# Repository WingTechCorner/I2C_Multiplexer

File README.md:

# Wing's I2C Multiplexer

- Multiple I2C devices with the same address on the same bus.
- Not full duplex. Only one device active at any one time.
- Performs MUX'ing via 4052D IC

# Files/Folders

- `platformio.ini` PlatformIO project config file
- `./src/` Source code
- `./hardware/` Various hardware design files.

# Datasheets

- 4052D Dual 4-Channel Analog Multiplexer, Demultiplexer
  - [Nexperia 74HC4052D Datasheet from LCSC](https://datasheet.lcsc.com/szlcsc/Nexperia-74HC4052D-653_C11350.pdf)

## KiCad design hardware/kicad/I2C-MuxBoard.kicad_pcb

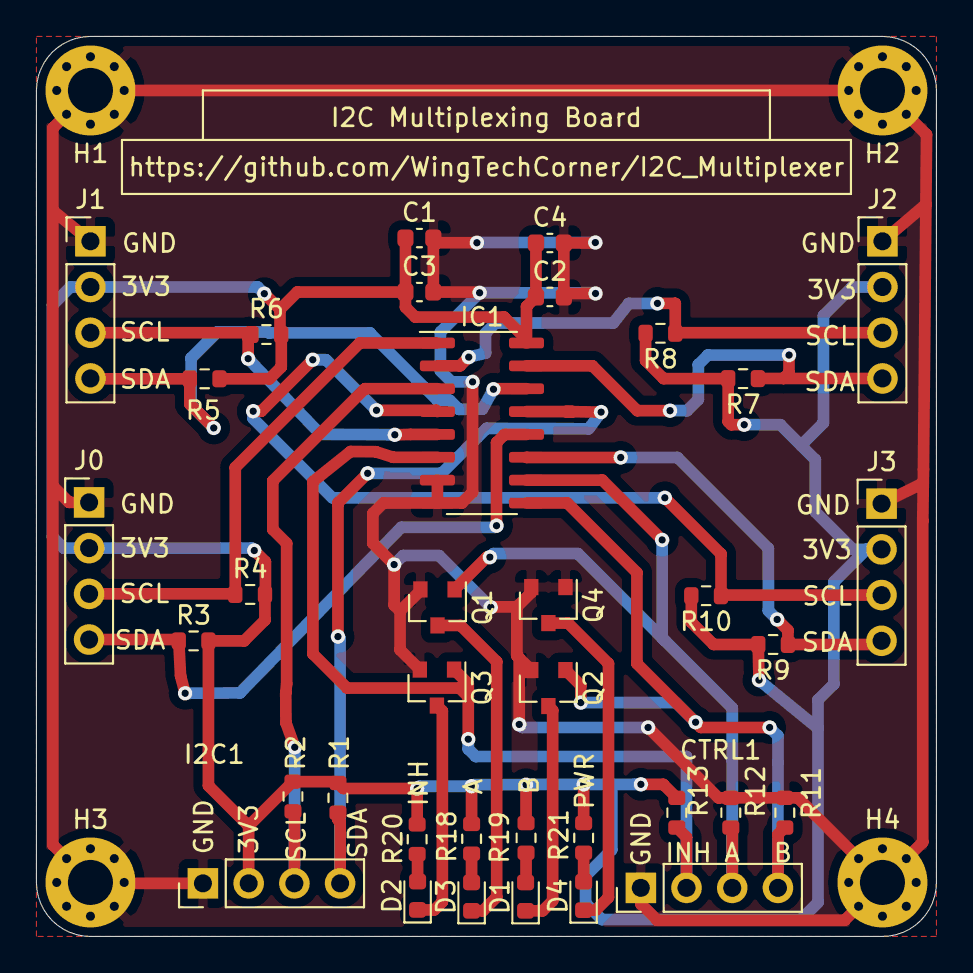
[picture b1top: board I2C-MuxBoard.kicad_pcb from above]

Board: 2 copper layers, 50.0 x 50.0 mm, 40 parts (0 on the bottom side), 23 nets.

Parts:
C1, C3: 4.7nF-50V-0603; C_0603_1608Metric
C2, C4: 10nF-50V-0603; C_0603_1608Metric
CTRL1: Conn_01x04; PinHeader_1x04_P2.54mm_Vertical
D1, D2, D3, D4: BLUE_LED; D_0603_1608Metric
H1, H2, H3, H4: MountingHole_Pad; MountingHole_2.5mm_Pad_Via
I2C1: Conn_01x04; PinHeader_1x04_P2.54mm_Vertical
IC1: CD4052B; SOIC-16_3.9x9.9mm_P1.27mm
J0, J1, J2, J3: Conn_01x04; PinHeader_1x04_P2.54mm_Vertical
Q1, Q2, Q3, Q4: AO3400A; SOT-23
R1, R2, R3, R4, R5, R6, R7, R8, R9, R10, R11, R12, R13: 10KOhms-±1%-1_10W-0603; R_0603_1608Metric
R18, R19, R20, R21: 470Ohms-±1%-1_10W-0603; R_0603_1608Metric

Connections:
3V3: C1.1, C2.1, C3.1, C4.1, I2C1.2, IC1.16, J0.2, J1.2, J2.2, J3.2, R1.2, R2.2, R3.2, R4.2, R5.2, R6.2, R7.2, R8.2, R9.2, R10.2, R13.2, R18.1, R19.1, R20.1, R21.1
ADDR-A: CTRL1.3, IC1.10, Q1.1, R12.1
ADDR-B: CTRL1.4, IC1.9, Q2.1, R11.1
GND: C1.2, C2.2, C3.2, C4.2, CTRL1.1, H1.1, H2.1, H3.1, H4.1, I2C1.1, IC1.7, IC1.8, J0.1, J1.1, J2.1, J3.1, Q1.2, Q2.2, Q3.2, Q4.1, Q4.2, R11.2, R12.2
INH: CTRL1.2, IC1.6, Q3.1, R13.1
unnamed: D1.1, Q2.3
unnamed: D1.2, R19.2
unnamed: D2.1, Q3.3
unnamed: D2.2, R20.2
unnamed: D3.1, Q1.3
unnamed: D3.2, R18.2
unnamed: D4.1, Q4.3
unnamed: D4.2, R21.2
P0-SCL: IC1.1, J0.3, R4.1
P0-SDA: IC1.12, J0.4, R3.1
P1-SCL: IC1.5, J1.3, R6.1
P1-SDA: IC1.14, J1.4, R5.1
P2-SCL: IC1.2, J2.3, R8.1
P2-SDA: IC1.15, J2.4, R7.1
P3-SCL: IC1.4, J3.3, R10.1
P3-SDA: IC1.11, J3.4, R9.1
SCL: I2C1.3, IC1.3, R2.1
SDA: I2C1.4, IC1.13, R1.1

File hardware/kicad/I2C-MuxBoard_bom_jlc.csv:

"Comment","Designator","Footprint","LCSC Part #"
"4.7nF-50V-0603","C1,C3","C_0603_1608Metric","C53987"
"10nF-50V-0603","C2,C4","C_0603_1608Metric","C57112"
"BLUE_LED","D1,D3,D2,D4","D_0603_1608Metric","C72041"
"CD4052B","IC1","SOIC-16_3.9x9.9mm_P1.27mm","C6521"
"AO3400A","Q2,Q3,Q1,Q4","SOT-23","C20917"
"10KOhms-±1%-1_10W-0603","R3,R4,R5,R6,R7,R8,R9,R10,R11,R12,R13,R1,R2","R_0603_1608Metric","C25804"
"470Ohms-±1%-1_10W-0603","R19,R18,R20,R21","R_0603_1608Metric","C23179"

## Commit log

2020-10-31 Initial Commit of working platformio project
2020-11-02 Adding KiCad design files, GERBER files, BOM, and CPL files.
2020-11-02 Images
2020-11-02 Image compression
2020-11-02 Updated main.cpp to remove unused variables, and changed delays to I2C get to work around cases of buffered I2C commands that get garbled if I2C bus switched before completion.
2020-11-02 Updated example main.cpp. Moved I2C getPixel into selection routine. Changed DrawPixel to INVERSE and not just WHITE or BLACK.

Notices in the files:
hardware/kicad/I2C-MuxBoard.kicad_pcb:
(C)Copyright 2020, Wing Tang Wong
